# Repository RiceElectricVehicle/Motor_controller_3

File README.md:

# Motor_controller_3

Upload any files relating to motor controller 3 here 
PCB files will be uploaded, as well as any documentation done on the controller

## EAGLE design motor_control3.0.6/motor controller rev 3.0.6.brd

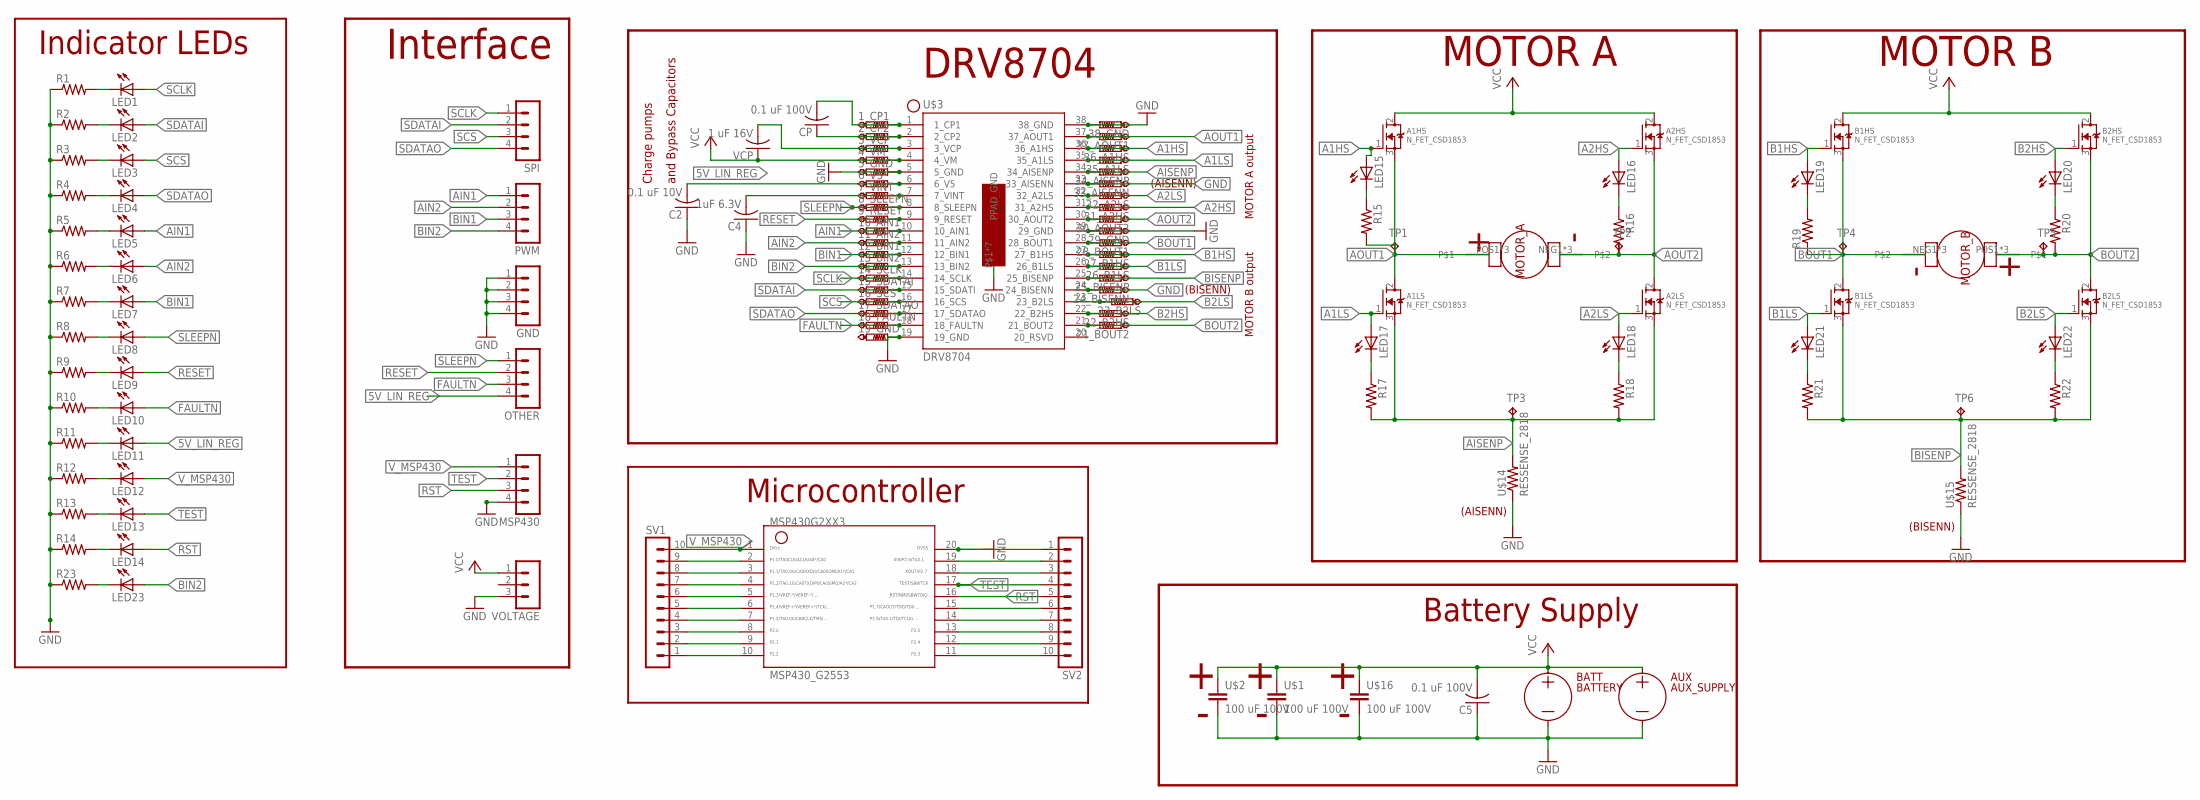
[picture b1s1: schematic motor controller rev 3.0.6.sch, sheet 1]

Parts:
1_CP1, 2_CP2, 3_VCP, 4_VM, 5_GND, 6_V5, 7_VINT, 8_SLEEPN, 9_RESET, 10_AIN1, 11_AIN2, 12_BIN1, 13_BIN2, 14_SCLK, 15_SDATAI, 16_SCS, 17_SDATAO, 18_FAULTN, 19_GND, 21_BOUT2, 22_B2HS, 23_B2LS, 24_BISENN, 25_BISENP, 26_B1LS, 27_B1HS, 28_BOUT1, 29_GND, 30_AOUT2, 31_A2HS, 32_A2LS, 33_AISENN, 34_AISENP, 35_A1LS, 36_A1HS, 37_AOUT1, 38_GND: PTR1TP10R; TP10R
A1HS, A1LS, A2HS, A2LS: N_FET_CSD1853; GDS_NFET
AUX: AUX_SUPPLY; PP14-45_RIGHT_ANGLE
B1HS, B1LS, B2HS, B2LS: N_FET_CSD1853; GDS_NFET
BATT: BATTERY; SB50POWER_CLAW
C2: 0.1 uF 10V; C0805K
C4: 1uF 6.3V; C0805K
C5: 0.1 uF 100V; C0805K
CP: 0.1 uF 100V; C0805K
GND: MA04-1
LED1, LED2, LED3, LED4, LED5, LED6, LED7, LED8, LED9, LED10, LED11, LED12, LED13, LED14, LED15, LED16, LED17, LED18, LED19, LED20, LED21, LED22, LED23: LEDCHIPLED_0805; CHIPLED_0805
MOTOR_A: MOTOR; SB50POWER_CLAW
MOTOR_B: MOTOR; SB50POWER_CLAW
MSP430: MA04-1
MSP430_G2553: G2XX3---N20; N20
OTHER: MA04-1
PWM: MA04-1
R1, R2, R3, R4, R5, R6, R7, R8, R9, R10, R11, R12, R13, R14, R15, R16, R17, R18, R19, R20, R21, R22, R23: R-US_R0805; R0805
SPI: MA04-1
SV1, SV2: MA10-1
TP1, TP2, TP3, TP4, TP5, TP6: TPB2,54; B2,54
U$1, U$2, U$16: 100 uF 100V; UCY_HD_CAP
U$3: DRV8704; HTSSOP-38
U$14, U$15: RESSENSE_2818; 2818_WITH_VIA
VCP: 1 uF 16V; C0805K
VOLTAGE: MA03-1

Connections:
1_CP1: 1_CP1.TP, CP.2, U$3.1 (1_CP1)
2_CP2: 2_CP2.TP, CP.1, U$3.2 (2_CP2)
5V_LIN_REG: 6_V5.TP, C2.2, LED11.A, OTHER.4, U$3.6 (6_V5)
A1HS: 36_A1HS.TP, A1HS.1 (G), LED15.A, U$3.36 (36_A1HS)
A1LS: 35_A1LS.TP, A1LS.1 (G), LED17.A, U$3.35 (35_A1LS)
A2HS: 31_A2HS.TP, A2HS.1 (G), LED16.A, U$3.31 (31_A2HS)
A2LS: 32_A2LS.TP, A2LS.1 (G), LED18.A, U$3.32 (32_A2LS)
AIN1: 10_AIN1.TP, LED5.A, PWM.1, U$3.10 (10_AIN1)
AIN2: 11_AIN2.TP, LED6.A, PWM.2, U$3.11 (11_AIN2)
AISENP: 34_AISENP.TP, A1LS.3 (S), A2LS.3 (S), R17.2, R18.2, TP3.TP, U$3.34 (34_AISENP), U$14.P2.2 (2), U$14.P$2 (2)
AOUT1: 37_AOUT1.TP, A1HS.3 (S), A1LS.2 (D), MOTOR_A.POS1, MOTOR_A.POS2, MOTOR_A.POS3, R15.2, TP1.TP, U$3.37 (37_AOUT1)
AOUT2: 30_AOUT2.TP, A2HS.3 (S), A2LS.2 (D), MOTOR_A.NEG1, MOTOR_A.NEG2, MOTOR_A.NEG3, R16.2, TP2.TP, U$3.30 (30_AOUT2)
B1HS: 27_B1HS.TP, B1HS.1 (G), LED19.A, U$3.27 (27_B1HS)
B1LS: 26_B1LS.TP, B1LS.1 (G), LED21.A, U$3.26 (26_B1LS)
B2HS: 22_B2HS.TP, B2HS.1 (G), LED20.A, U$3.22 (22_B2HS)
B2LS: 23_B2LS.TP, B2LS.1 (G), LED22.A, U$3.23 (23_B2LS)
BIN1: 12_BIN1.TP, LED7.A, PWM.3, U$3.12 (12_BIN1)
BIN2: 13_BIN2.TP, LED23.A, PWM.4, U$3.13 (13_BIN2)
BISENP: 25_BISENP.TP, B1LS.3 (S), B2LS.3 (S), R21.2, R22.2, TP6.TP, U$3.25 (25_BISENP), U$15.P2.2 (2), U$15.P$2 (2)
BOUT1: 28_BOUT1.TP, B1HS.3 (S), B1LS.2 (D), MOTOR_B.NEG1, MOTOR_B.NEG2, MOTOR_B.NEG3, R19.1, TP4.TP, U$3.28 (28_BOUT1)
BOUT2: 21_BOUT2.TP, B2HS.3 (S), B2LS.2 (D), MOTOR_B.POS1, MOTOR_B.POS2, MOTOR_B.POS3, R20.2, TP5.TP, U$3.21 (21_BOUT2)
FAULTN: 18_FAULTN.TP, LED10.A, OTHER.3, U$3.18 (18_FAULTN)
GND: 5_GND.TP, 19_GND.TP, 24_BISENN.TP, 29_GND.TP, 33_AISENN.TP, 38_GND.TP, AUX.P$1 (-), BATT.NEG1 (-), BATT.NEG2 (-), BATT.NEG3 (-), C2.1, C4.1, C5.1, GND.1, GND.2, GND.3, GND.4, MSP430.4, MSP430_G2553.20, R1.1, R2.1, R3.1, R4.1, R5.1, R6.1, R7.1, R8.1, R9.1, R10.1, R11.1, R12.1, R13.1, R14.1, R23.1, SV2.1, U$1.-, U$2.-, U$3.5 (5_GND), U$3.19 (19_GND), U$3.24 (24_BISENN), U$3.29 (29_GND), U$3.33 (33_AISENN), U$3.38 (38_GND), U$3.P$1 (PPAD_GND), U$3.P$2 (PPAD_GND), U$3.P$3 (PPAD_GND), U$3.P$4 (PPAD_GND), U$3.PPAD0 (PPAD_GND), U$3.PPAD1 (PPAD_GND), U$3.PPAD2 (PPAD_GND), U$14.P1.1 (1), U$14.P$1 (1), U$15.P1.1 (1), U$15.P$1 (1), U$16.-, VOLTAGE.3
unnamed: MSP430_G2553.2, SV1.9
unnamed: MSP430_G2553.3, SV1.8
unnamed: MSP430_G2553.4, SV1.7
unnamed: MSP430_G2553.5, SV1.6
unnamed: MSP430_G2553.6, SV1.5
unnamed: MSP430_G2553.7, SV1.4
unnamed: MSP430_G2553.8, SV1.3
unnamed: MSP430_G2553.9, SV1.2
unnamed: MSP430_G2553.10, SV1.1
unnamed: MSP430_G2553.11, SV2.10
unnamed: MSP430_G2553.12, SV2.9
unnamed: MSP430_G2553.13, SV2.8
unnamed: MSP430_G2553.14, SV2.7
unnamed: MSP430_G2553.15, SV2.6
unnamed: MSP430_G2553.18, SV2.3
unnamed: MSP430_G2553.19, SV2.2
unnamed: LED1.C, R1.2
unnamed: LED2.C, R2.2
unnamed: LED3.C, R3.2
unnamed: LED4.C, R4.2
unnamed: LED5.C, R5.2
unnamed: LED6.C, R6.2
unnamed: LED7.C, R7.2
unnamed: LED15.C, R15.1
unnamed: LED17.C, R17.1
unnamed: LED18.C, R18.1
unnamed: LED16.C, R16.1
unnamed: LED19.C, R19.2
unnamed: LED20.C, R20.1
unnamed: LED22.C, R22.1
unnamed: LED21.C, R21.1
unnamed: LED23.C, R23.2
unnamed: LED14.C, R14.2
unnamed: LED13.C, R13.2
unnamed: LED12.C, R12.2
unnamed: LED11.C, R11.2
unnamed: LED10.C, R10.2
unnamed: LED9.C, R9.2
unnamed: LED8.C, R8.2
RESET: 9_RESET.TP, LED9.A, OTHER.2, U$3.9 (9_RESET)
RST: LED14.A, MSP430.3, MSP430_G2553.16, SV2.5
SCLK: 14_SCLK.TP, LED1.A, SPI.1, U$3.14 (14_SCLK)
SCS: 16_SCS.TP, LED3.A, SPI.3, U$3.16 (16_SCS)
SDATAI: 15_SDATAI.TP, LED2.A, SPI.2, U$3.15 (15_SDATI)
SDATAO: 17_SDATAO.TP, LED4.A, SPI.4, U$3.17 (17_SDATAO)
SLEEPN: 8_SLEEPN.TP, LED8.A, OTHER.1, U$3.8 (8_SLEEPN)
TEST: LED13.A, MSP430.2, MSP430_G2553.17, SV2.4
VCC: 4_VM.TP, A1HS.2 (D), A2HS.2 (D), AUX.P$2 (+), B1HS.2 (D), B2HS.2 (D), BATT.POS1 (+), BATT.POS2 (+), BATT.POS3 (+), C5.2, U$1.+, U$2.+, U$3.4 (4_VM), U$16.+, VCP.1, VOLTAGE.1
VCP: 3_VCP.TP, U$3.3 (3_VCP), VCP.2
VINT: 7_VINT.TP, C4.2, U$3.7 (7_VINT)
V_MSP430: LED12.A, MSP430.1, MSP430_G2553.1, SV1.10

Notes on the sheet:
MOTOR A
MOTOR B
DRV8704
MOTOR A output
MOTOR B output
Battery Supply
Charge pumps
and Bypass Capacitors
Interface
Microcontroller
Indicator LEDs
(BISENN)
(AISENN)

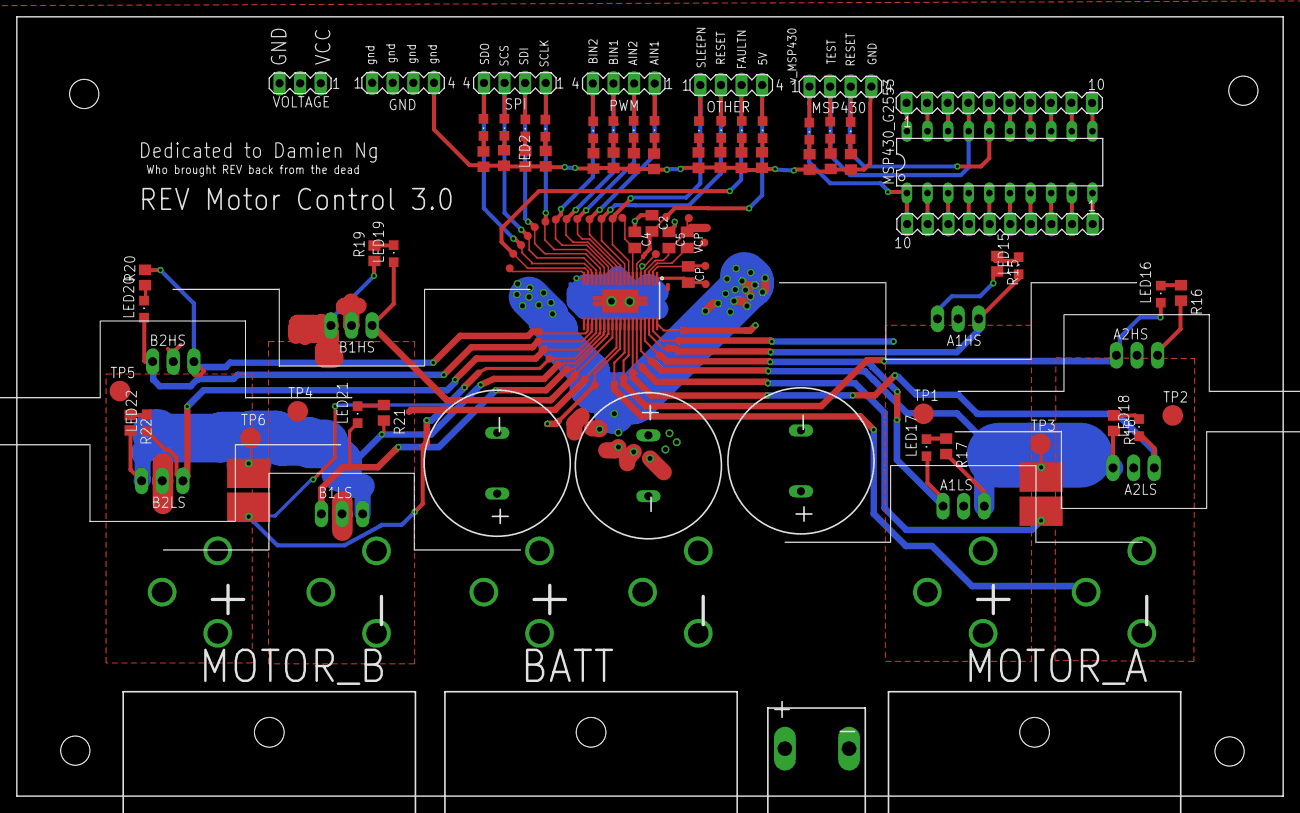
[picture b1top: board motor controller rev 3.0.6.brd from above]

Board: 2 copper layers, 156.0 x 96.0 mm, 121 parts (0 on the bottom side), 74 nets.
